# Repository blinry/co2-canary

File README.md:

# 🐤 CO2 Canary

An open-hardware, ultra-low power CO2 sensor.

## Features

- Battery life of at least 6 months
- Uses the [Senseair Sunlight CO2](https://senseair.com/product/sunlight-co2/)
    - Measurement range: 400-10000 ppm
    - Accuracy of +/- 50 ppm
    - Self-calibrating
- Shows a graph of the CO2 level over time
- Connectivity possible via Wifi, Bluetooth Low Energy, or Zigbee/Thread (not implemented yet)
- Connect a LiPo battery via the JST PH 2.0 connector, and charge via USB-C
    - Or connect your own power source to the *BAT* and *GND* pins

## Hardware

You can find the hardware design files in the [hardware](hardware) directory. The design was made using KiCad, and I've been using JLCPCB for manufacturing.

I'm hoping to write detailed instructions for how to order and assemble the device here soon. Until the following problems are fixed, I'd suggest you wait before you order one.

### Known problems for v0.1.0

- The battery level indicator chip is not connected correctly – it will not work as-is.
- The *reset* and *boot* buttons are not labelled on the board.

## Firmware

The firmware is located in the [firmware](firmware) directory. It's written in [no-std](https://docs.rust-embedded.org/book/intro/no-std.html) Rust, using the [esp-hal](https://github.com/esp-rs/esp-hal) crate.

## Acknowledgements

Many people helped me while working on this project! I'm deeply grateful for your support, this project would not have been possible without you.

## Licenses

The CO2 Canary is open hardware:

- The hardware design is licensed under the [CERN Open Hardware Licence v2](https://ohwr.org/cern_ohl_s_v2.txt) or any later version.
- The firmware is licensed under the [GNU General Public Licence v3.0](https://www.gnu.org/licenses/gpl-3.0.en.html) or any later version.

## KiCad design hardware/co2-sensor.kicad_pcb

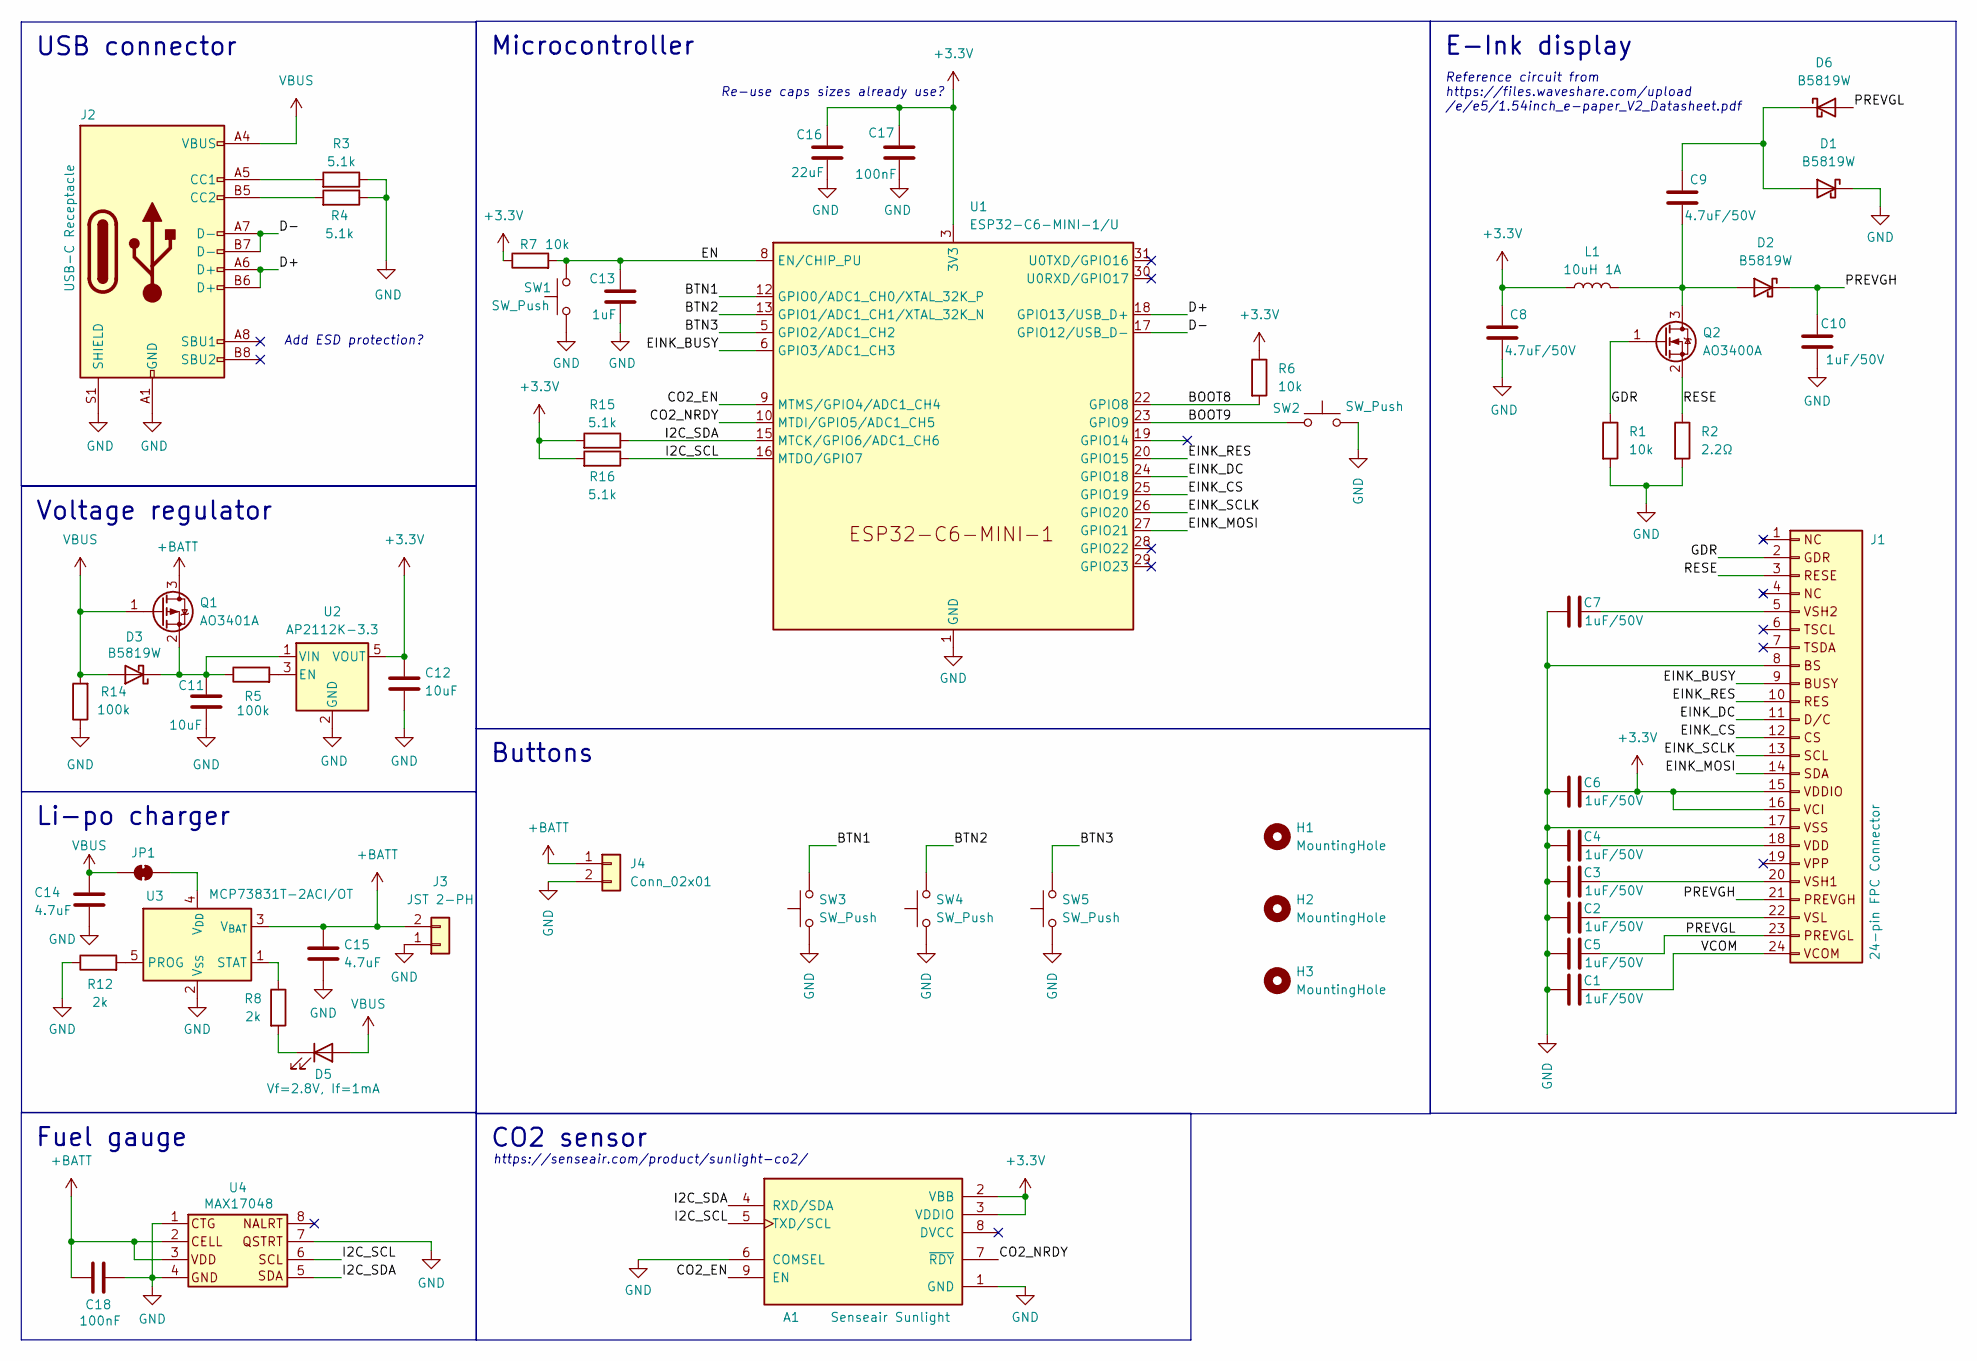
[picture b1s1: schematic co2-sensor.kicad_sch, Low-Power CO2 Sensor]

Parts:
A1: Senseair Sunlight; Senseair_Sunrise; PARTREV 1.00.000
C1, C2, C3, C4, C5, C6, C7, C10: 1uF/50V; C_0603_1608Metric; LCSC Part C15849
C8, C9: 4.7uF/50V; C_1206_3216Metric; LCSC Part C29823
C11, C12: 10uF; C_0603_1608Metric; LCSC Part C96446
C13: 1uF; C_0603_1608Metric; LCSC Part C15849
C14, C15: 4.7uF; C_1206_3216Metric; LCSC Part C29823
C16: 22uF; C_0805_2012Metric; LCSC Part C45783
C17, C18: 100nF; C_0805_2012Metric; LCSC Part C1710
D1, D2, D3, D6: B5819W; D_SOD-123; LCSC Part C8598
D5: Vf=2.8V, If=1mA; LED_0603_1608Metric; LCSC Part C2290
H1, H2, H3: MountingHole; MountingHole_2.2mm_M2
J1: 24-pin FPC Connector; Jushuo_AFC07-S24FCA-00_1x24-1MP_P0.50_Horizontal; LCSC Part C262643
J2: USB-C Receptacle; USB_C_Receptacle_G-Switch_GT-USB-7010ASV; LCSC Part C2988369
J3: JST 2-PH; JST_PH_S2B-PH-SM4-TB_1x02-1MP_P2.00mm_Horizontal; LCSC Part C7433648
J4: Conn_02x01; PinHeader_1x02_P2.54mm_Vertical
JP1: SolderJumper_2_Bridged; SolderJumper-2_P1.3mm_Bridged_RoundedPad1.0x1.5mm
L1: 10uH 1A; L_1008_2520Metric; LCSC Part C602018
Q1: AO3401A; SOT-23; LCSC Part C15127
Q2: AO3400A; SOT-23; LCSC Part C20917
R1, R6, R7: 10k; R_0603_1608Metric; LCSC Part C25804
R2: 2.2Ω; R_0603_1608Metric; LCSC Part C22939
R3, R4, R15, R16: 5.1k; R_0603_1608Metric; LCSC Part C23186
R5, R14: 100k; R_0402_1005Metric; LCSC Part C25741
R8, R12: 2k; R_0402_1005Metric; LCSC Part C4109
SW1, SW2, SW3, SW4, SW5: SW_Push; TS24CA; LCSC Part C318884
U1: ESP32-C6-MINI-1/U; ESP32-C6-MINI-1; LCSC Part C5736265
U2: AP2112K-3.3; SOT-23-5; LCSC Part C51118
U3: MCP73831T-2ACI/OT; SOT-23-5; LCSC Part C424093
U4: MAX17048; DFN-8-1EP_2x2mm_P0.5mm_EP1.05x1.75mm; LCSC Part C2682616

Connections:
+3.3V: A1.2 (VBB), A1.3 (VDDIO), C6.2, C8.2, C12.1, C16.2, C17.2, J1.15, J1.16, L1.1, R6.1, R7.1, R15.2, R16.2, U1.3 (3V3), U2.5 (VOUT)
+BATT: C15.1, C18.2, J3.2, J4.1, Q1.3 (D), U3.3 (V_{BAT}), U4.2, U4.3
/BOOT8: R6.2, U1.22 (GPIO8)
/BOOT9: SW2.2, U1.23 (GPIO9)
/BTN1: SW3.2, U1.12 (GPIO0/ADC1_CH0/XTAL_32K_P)
/BTN2: SW4.2, U1.13 (GPIO1/ADC1_CH1/XTAL_32K_N)
/BTN3: SW5.2, U1.5 (GPIO2/ADC1_CH2)
/CO2_EN: A1.9 (EN), U1.9 (MTMS/GPIO4/ADC1_CH4)
/CO2_NRDY: A1.7 (~RDY), U1.10 (MTDI/GPIO5/ADC1_CH5)
/D+: J2.A6 (D+), J2.B6 (D+), U1.18 (GPIO13/USB_D+)
/D-: J2.A7 (D-), J2.B7 (D-), U1.17 (GPIO12/USB_D-)
/EINK_BUSY: J1.9, U1.6 (GPIO3/ADC1_CH3)
/EINK_CS: J1.12, U1.25 (GPIO19)
/EINK_DC: J1.11, U1.24 (GPIO18)
/EINK_MOSI: J1.14, U1.27 (GPIO21)
/EINK_RES: J1.10, U1.20 (GPIO15)
/EINK_SCLK: J1.13, U1.26 (GPIO20)
/EN: C13.2, R7.2, SW1.2, U1.8 (EN/CHIP_PU)
/GDR: J1.2, Q2.1 (G), R1.1
/I2C_SCL: A1.5 (TXD/SCL), R16.1, U1.16 (MTDO/GPIO7), U4.6
/I2C_SDA: A1.4 (RXD/SDA), R15.1, U1.15 (MTCK/GPIO6/ADC1_CH6), U4.5
/PREVGH: C10.2, D2.1 (K), J1.21
/PREVGL: C5.2, D6.2 (A), J1.23
/RESE: J1.3, Q2.2 (S), R2.1
/VCOM: C1.2, J1.24
GND: A1.1 (GND), A1.6 (COMSEL), C1.1, C2.1, C3.1, C4.1, C5.1, C6.1, C7.1, C8.1, C10.1, C11.2, C12.2, C13.1, C14.2, C15.2, C16.1, C17.1, C18.1, D1.1 (K), J1.8, J1.17, J2.A1 (GND), J2.A12 (GND), J2.B1 (GND), J2.B12 (GND), J2.S1 (SHIELD), J3.1, J4.2, R1.2, R2.2, R3.1, R4.1, R12.1, R14.1, SW1.1, SW2.1, SW3.1, SW4.1, SW5.1, U1.1 (GND), U1.2 (GND), U1.11 (GND), U1.14 (GND), U1.36 (GND), U1.37 (GND), U1.38 (GND), U1.39 (GND), U1.40 (GND), U1.41 (GND), U1.42 (GND), U1.43 (GND), U1.44 (GND), U1.45 (GND), U1.46 (GND), U1.47 (GND), U1.48 (GND), U1.49 (GND), U1.50 (GND), U1.51 (GND), U1.52 (GND), U1.53 (GND), U2.2 (GND), U3.2 (V_{SS}), U4.1, U4.4, U4.7
unnamed: C9.2, D1.2 (A), D6.1 (K)
unnamed: C9.1, D2.2 (A), L1.2, Q2.3 (D)
unnamed: C11.1, D3.1 (K), Q1.2 (S), R5.1, U2.1 (VIN)
unnamed: D5.1 (K), R8.2
unnamed: C7.2, J1.5
unnamed: C4.2, J1.18
unnamed: C3.2, J1.20
unnamed: C2.2, J1.22
unnamed: J2.A5 (CC1), R3.2
unnamed: J2.B5 (CC2), R4.2
unnamed: JP1.2 (B), U3.4 (V_{DD})
unnamed: R5.2, U2.3 (EN)
unnamed: R12.2, U3.5 (PROG)
unnamed: R8.1, U3.1 (STAT)
VBUS: C14.1, D3.2 (A), D5.2 (A), J2.A4 (VBUS), J2.A9 (VBUS), J2.B4 (VBUS), J2.B9 (VBUS), JP1.1 (A), Q1.1 (G), R14.2

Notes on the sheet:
https://senseair.com/product/sunlight-co2/
Add ESD protection?
Re-use caps sizes already use?
Reference circuit from https://files.waveshare.com/upload /e/e5/1.54inch_e-paper_V2_Datasheet.pdf
Fuel gauge
Buttons
USB connector
Voltage regulator
Microcontroller
E-Ink display
Li-po charger
CO2 sensor

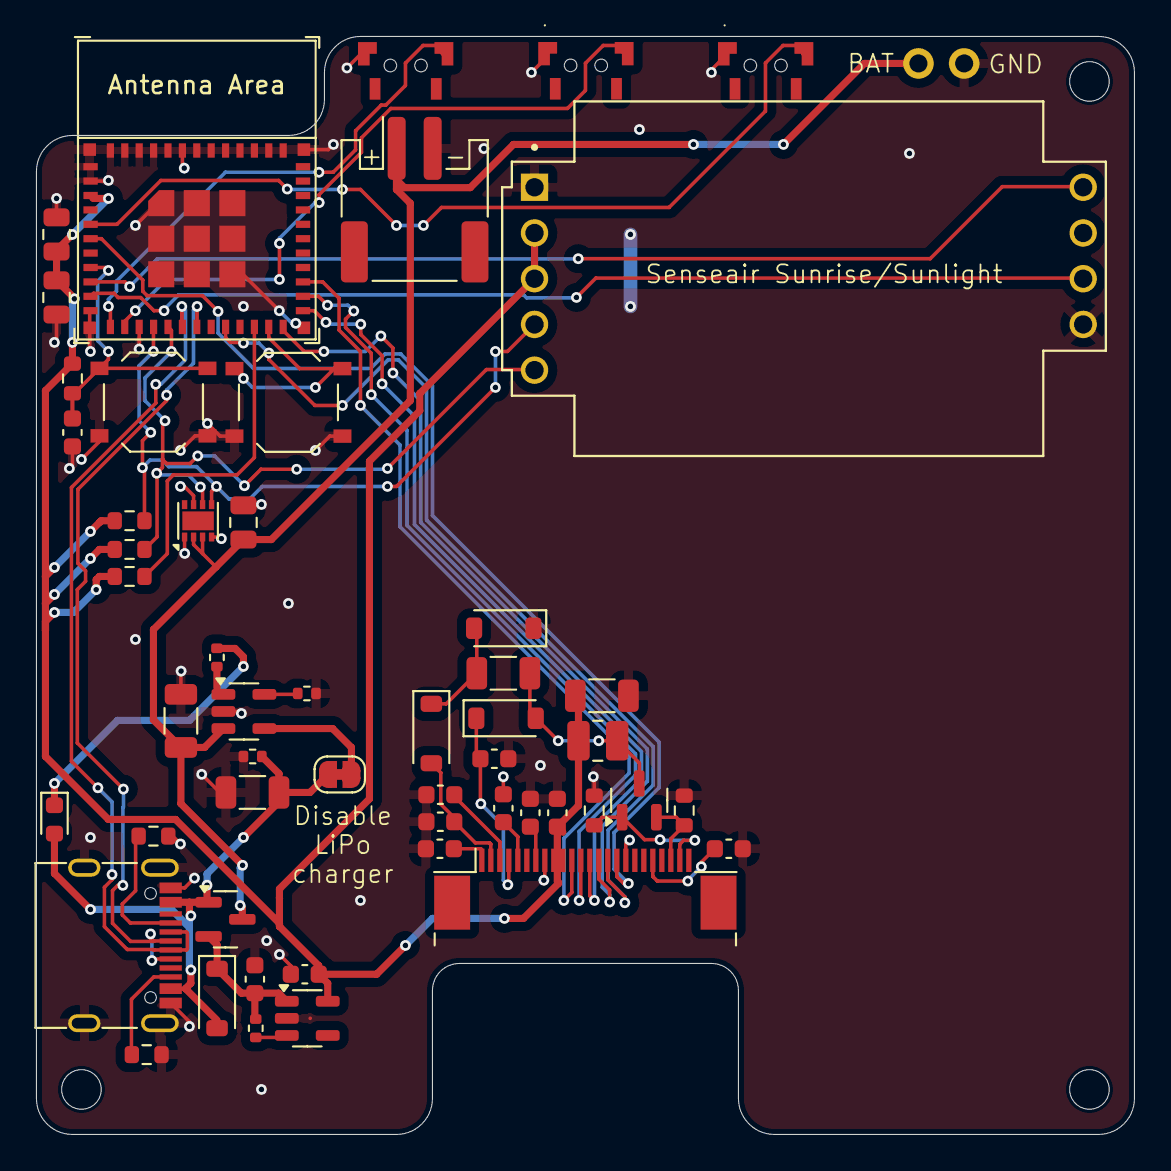
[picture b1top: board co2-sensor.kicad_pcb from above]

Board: 2 copper layers, 61.0 x 61.0 mm, 56 parts (0 on the bottom side), 41 nets.

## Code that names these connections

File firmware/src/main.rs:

#![no_std]
#![no_main]
// Allow this for now, to be able to use ram(rtc_fast).
#![allow(static_mut_refs)]

mod display;
mod history;
mod sunrise;

use core::time::Duration;
use display::Display;
use history::History;
use sunrise::{CalibrationData, SunriseSensor};

use embedded_hal_bus::spi::ExclusiveDevice;
use esp_backtrace as _;
use esp_hal::{
    delay::Delay,
    gpio::{Input, InputConfig, Level, Output, OutputConfig, Pull},
    i2c::master::{Config as I2cConfig, I2c},
    ram,
    rtc_cntl::{sleep::TimerWakeupSource, Rtc},
    spi::master::{Config as SpiConfig, Spi},
    time::{Instant, Rate},
};
use esp_println::println;

#[ram(rtc_fast)]
static mut HISTORY: History = History::new();

#[ram(rtc_fast)]
static mut CALIBRATION_DATA: CalibrationData = CalibrationData::new();

#[ram(rtc_fast)]
static mut LAST_DISPLAYED_CO2: u16 = 0;

#[esp_hal::main]
fn main() -> ! {
    let wakeup_time = Instant::now();

    let peripherals = esp_hal::init(esp_hal::Config::default());
    let mut delay = Delay::new();
    let mut rtc = Rtc::new(peripherals.LPWR);

    let mut temperature = 0.0;

    let i2c_config = I2cConfig::default().with_frequency(Rate::from_khz(100));
    let i2c = I2c::new(peripherals.I2C0, i2c_config)
        .expect("Should be able to configure I2C peripheral")
        .with_sda(peripherals.GPIO6)
        .with_scl(peripherals.GPIO7);

    if true {
        let co2_enable = Output::new(peripherals.GPIO4, Level::High, OutputConfig::default());

        let number_of_samples = 2;
        let mut co2_sensor = SunriseSensor::new(i2c, co2_enable, &mut delay);
        co2_sensor
            .init(number_of_samples)
            .expect("Could not initialize CO2 sensor");

        unsafe {
            co2_sensor
                .start_measurement(Some(&CALIBRATION_DATA))
                .expect("Could not start CO2 measurement");
        }

        // TODO: I can probably lower this?
        let milliseconds_per_sample = 300u64;
        let timer = TimerWakeupSource::new(Duration::from_millis(
            u64::from(number_of_samples) * milliseconds_per_sample,
        ));
        rtc.sleep_light(&[&timer]);

        unsafe {
            match co2_sensor.get_co2(&mut CALIBRATION_DATA) {
                Ok(co2) => {
                    println!("CO2: {co2} ppm");
                    HISTORY.add_measurement(co2);
                }
                Err(error) => {
                    println!("Error: {error:?}");
                    HISTORY.add_measurement(0);
                }
            }
            CALIBRATION_DATA.update_time_ms(rtc.time_since_boot().as_millis());
            println!("{:?}", CALIBRATION_DATA);
        }

        temperature = co2_sensor.get_temperature().unwrap();

        co2_sensor.turn_off();
        let _i2c = co2_sensor.release();
    }

    let battery_percent = None;

    // Disabled for v0.1.0, where the MAX17048 chip is not connected correctly.
    // let battery_percent = Some(
    //     max170xx::Max17048::new(i2c)
    //         .soc()
    //         .expect("Should be able to read state of charge"),
    // );

    // Refresh the display if the CO2 value has changed by more than a certain amount.
    let refresh_threshold = 50; // ppm
    let refresh_display =
        unsafe { HISTORY.recent().unwrap_or(0).abs_diff(LAST_DISPLAYED_CO2) >= refresh_threshold };

    if refresh_display {
        let mut spi = Spi::new(peripherals.SPI2, SpiConfig::default())
            .expect("Should be able to configure SPI device")
            .with_sck(peripherals.GPIO20)
            .with_mosi(peripherals.GPIO21);

        let cs = Output::new(peripherals.GPIO19, Level::High, OutputConfig::default()); // chip select
        let busy_in = Input::new(
            peripherals.GPIO3,
            InputConfig::default().with_pull(Pull::Down),
        );
        let dc = Output::new(peripherals.GPIO18, Level::Low, OutputConfig::default()); // data/command
        let rst = Output::new(peripherals.GPIO15, Level::Low, OutputConfig::default());

        let exclusive_spi = ExclusiveDevice::new(&mut spi, cs, &mut delay)
            .expect("Failed to get exclusive SPI device");
        let mut delay = Delay::new();

        let mut display = Display::new(exclusive_spi, busy_in, dc, rst, &mut delay);

        unsafe {
            display
                .draw(&HISTORY, temperature, battery_percent)
                .expect("Failed to draw to the display");
            LAST_DISPLAYED_CO2 = HISTORY.recent().unwrap_or(0);
        }
    }

    // Deep sleep.
    let wakeup_interval = Duration::from_secs(30);
    let awake_duration = Instant::now() - wakeup_time;
    // (Convert to std Duration.)
    let awake_duration = Duration::from_millis(awake_duration.as_millis());
    let remaining_time = wakeup_interval - awake_duration;
    let timer = TimerWakeupSource::new(remaining_time);
    rtc.sleep_deep(&[&timer]);
}

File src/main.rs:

#![no_std]
#![no_main]
// Allow this for now, to be able to use ram(rtc_fast).
#![allow(static_mut_refs)]

mod display;
mod history;
mod sunrise;

use core::time::Duration;
use display::Display;
use history::History;
use sunrise::{CalibrationData, SunriseSensor};

use embedded_hal_bus::spi::ExclusiveDevice;
use esp_backtrace as _;
use esp_hal::{
    delay::Delay,
    gpio::{Input, InputConfig, Level, Output, OutputConfig, Pull},
    i2c::master::{Config as I2cConfig, I2c},
    ram,
    rtc_cntl::{sleep::TimerWakeupSource, Rtc},
    spi::master::{Config as SpiConfig, Spi},
    time::{Instant, Rate},
};
use esp_println::println;

#[ram(rtc_fast)]
static mut HISTORY: History = History::new();

#[ram(rtc_fast)]
static mut CALIBRATION_DATA: CalibrationData = CalibrationData::new();

#[ram(rtc_fast)]
static mut LAST_DISPLAYED_CO2: u16 = 0;

#[esp_hal::main]
fn main() -> ! {
    let wakeup_time = Instant::now();

    let peripherals = esp_hal::init(esp_hal::Config::default());
    let mut delay = Delay::new();
    let mut rtc = Rtc::new(peripherals.LPWR);

    let mut neopixel_and_i2c_power =
        Output::new(peripherals.GPIO20, Level::Low, OutputConfig::default());

    let mut temperature = 0.0;

    // Required for I2C to work!
    neopixel_and_i2c_power.set_high();

    let i2c_config = I2cConfig::default().with_frequency(Rate::from_khz(100));
    let mut i2c = I2c::new(peripherals.I2C0, i2c_config)
        .expect("Should be able to configure I2C peripheral")
        .with_sda(peripherals.GPIO19)
        .with_scl(peripherals.GPIO18);

    if true {
        let co2_enable = Output::new(peripherals.GPIO3, Level::High, OutputConfig::default());

        let number_of_samples = 2;
        let mut co2_sensor = SunriseSensor::new(i2c, co2_enable, &mut delay);
        co2_sensor
            .init(number_of_samples)
            .expect("Could not initialize CO2 sensor");

        unsafe {
            co2_sensor
                .start_measurement(Some(&CALIBRATION_DATA))
                .expect("Could not start CO2 measurement");
        }

        // TODO: I can probably lower this?
        let milliseconds_per_sample = 300u64;
        let timer = TimerWakeupSource::new(Duration::from_millis(
            (number_of_samples as u64) * milliseconds_per_sample,
        ));
        rtc.sleep_light(&[&timer]);

        unsafe {
            match co2_sensor.get_co2(&mut CALIBRATION_DATA) {
                Ok(co2) => {
                    println!("CO2: {} ppm", co2);
                    HISTORY.add_measurement(co2);
                }
                Err(e) => {
                    println!("Error: {:?}", e);
                    HISTORY.add_measurement(0);
                }
            }
            CALIBRATION_DATA.update_time_ms(rtc.time_since_boot().as_millis());
            println!("{:?}", CALIBRATION_DATA);
        }

        temperature = co2_sensor.get_temperature().unwrap();

        co2_sensor.turn_off();
        i2c = co2_sensor.release();
    }

    let battery_percent = max170xx::Max17048::new(i2c).soc().ok();

    // Refresh the display if the CO2 value has changed by more than a certain amount.
    let refresh_threshold = 50; // ppm
    let refresh_display =
        unsafe { HISTORY.recent().unwrap_or(0).abs_diff(LAST_DISPLAYED_CO2) >= refresh_threshold };

    if refresh_display {
        let mut spi = Spi::new(peripherals.SPI2, SpiConfig::default())
            .expect("Should be able to configure SPI device")
            .with_sck(peripherals.GPIO21)
            .with_mosi(peripherals.GPIO22)
            .with_miso(peripherals.GPIO23);

        let cs = Output::new(peripherals.GPIO7, Level::High, OutputConfig::default()); // chip select
        let busy_in = Input::new(
            peripherals.GPIO5,
            InputConfig::default().with_pull(Pull::Down),
        );
        let dc = Output::new(peripherals.GPIO8, Level::Low, OutputConfig::default()); // data/command
        let rst = Output::new(peripherals.GPIO1, Level::Low, OutputConfig::default());

        let exclusive_spi = ExclusiveDevice::new(&mut spi, cs, &mut delay)
            .expect("Failed to get exclusive SPI device");
        let mut delay = Delay::new();

        let mut display = Display::new(exclusive_spi, busy_in, dc, rst, &mut delay);

        unsafe {
            display
                .draw(&HISTORY, temperature, battery_percent)
                .expect("Failed to draw to the display");
            LAST_DISPLAYED_CO2 = HISTORY.recent().unwrap_or(0);
        }
    }

    // Power off the neopixel and I2C bus, for low-power sleep.
    // See https://learn.adafruit.com/adafruit-esp32-c6-feather/low-power-use
    neopixel_and_i2c_power.set_low();

    // Deep sleep.
    let wakeup_interval = Duration::from_secs(30);
    let awake_duration = Instant::now() - wakeup_time;
    // (Convert to std Duration.)
    let awake_duration = Duration::from_millis(awake_duration.as_millis());
    let remaining_time = wakeup_interval - awake_duration;
    let timer = TimerWakeupSource::new(remaining_time);
    rtc.sleep_deep(&[&timer]);
}

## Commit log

2024-01-12 Access Sunrise sensor via I2C
2024-01-13 Run Sunrise in single measurement mode
2024-01-16 Draw test text on the e-ink screen
2024-01-16 Try to print CO2 value
2024-01-16 Display real CO2 data \o/
2024-01-17 Better sleep and depowering
2024-01-21 Try to draw a history
2024-01-30 Draw graph, kept in RTC memory
2024-02-01 Beginning of a Nix flake
2024-02-01 Update flake to a working state, thanks to knarkzel/esp32!
2024-02-02 Switch to small screen and clean up code
2024-02-02 Pretty font <3
2024-02-03 Pull out Sunrise logic into its own module
2024-02-03 Allow caller of CO2 sensor to light sleep
2024-02-03 Pull out display logic
2024-02-03 Factor out History struct
2024-02-04 Implement automatic background calibration
2024-02-04 Add temperature display
2024-02-04 Clippy improvements
2024-02-04 Increase SPI and I2C frequencies
2024-02-04 Display battery voltage
2024-02-10 Another guess for the battery factor. Maybe this one's better?
2024-10-19 Update crates
2024-10-19 More crate update adaptions
2024-10-19 Update flakes
2024-10-19 Adapt to new crates
2024-10-19 Fix Nix shell
2024-10-19 Make compile again
2024-10-19 Refactor out history into its own type
2024-10-19 System time is in microseconds, not milliseconds!
2024-10-19 Draw dashed line at 1000 ppm
2024-10-19 Black line behind number if critical value reached
2024-10-20 Add 0 measurements if CO2 measurement fails
2024-10-21 Fix graph display, keep same time-per-pixel in graph
2024-10-24 Don't change time axis resolution of graph over time
2024-10-25 Try to adapt to ESP32-C6, not working yet
2024-10-28 Make I2C work again
2024-10-28 Display battery percentage
2024-10-30 Initial commit, half-finished design with Feather
2024-10-31 Rework to use ESP32 module directly
2024-11-01 Polish before getting feedback
2024-11-09 Clean up unused code
2024-11-09 Refresh display only when the CO2 changes "enough"
2024-11-12 Thinner graph lines
2024-11-19 Add charging LED, make all wakeup sources trigger down
2024-11-19 Add .gitignore and some files I'm not sure I need to track
2024-11-19 Before manual de-bolding fix
2024-11-19 Fixed!
2024-11-19 Update PCB from schematic
2024-11-20 First test export
2024-11-21 Add all LCSC part numbers
2024-11-21 Move components around
2024-11-22 Move around some more
2025-02-25 Add Design Rules file for JLCPCB
2025-02-25 Start connecting components for the e-ink display
2025-02-25 Don't know?
2025-02-25 Apply some DRC tips
2025-02-25 Connect everything
2025-02-26 More tweaking
2025-02-27 Add labels and OSHW logo
2025-02-27 Rename variables to be more semantically correct
2025-02-27 Update all crates we depend on
2025-02-27 Switch to max170xx crate, because it uses embedded_hal 1.0
2025-02-28 Fix more distance violations
2025-02-28 Lower general clerance to 0.1 mm
2025-02-28 Add pins for providing BAT power
2025-02-28 Improve labels
2025-02-28 Final touches
2025-02-28 Move firmware to firmware/ subdirectory
2025-02-28 Move KiCad design to hardware/ subdirectory
2025-03-09 Start adapting to new PCB
2025-03-09 Adapt code for the assembled hardware version v0.1.0
2025-03-09 Start writing a README
2025-03-11 refactor: enable more lints and minor code improvements
